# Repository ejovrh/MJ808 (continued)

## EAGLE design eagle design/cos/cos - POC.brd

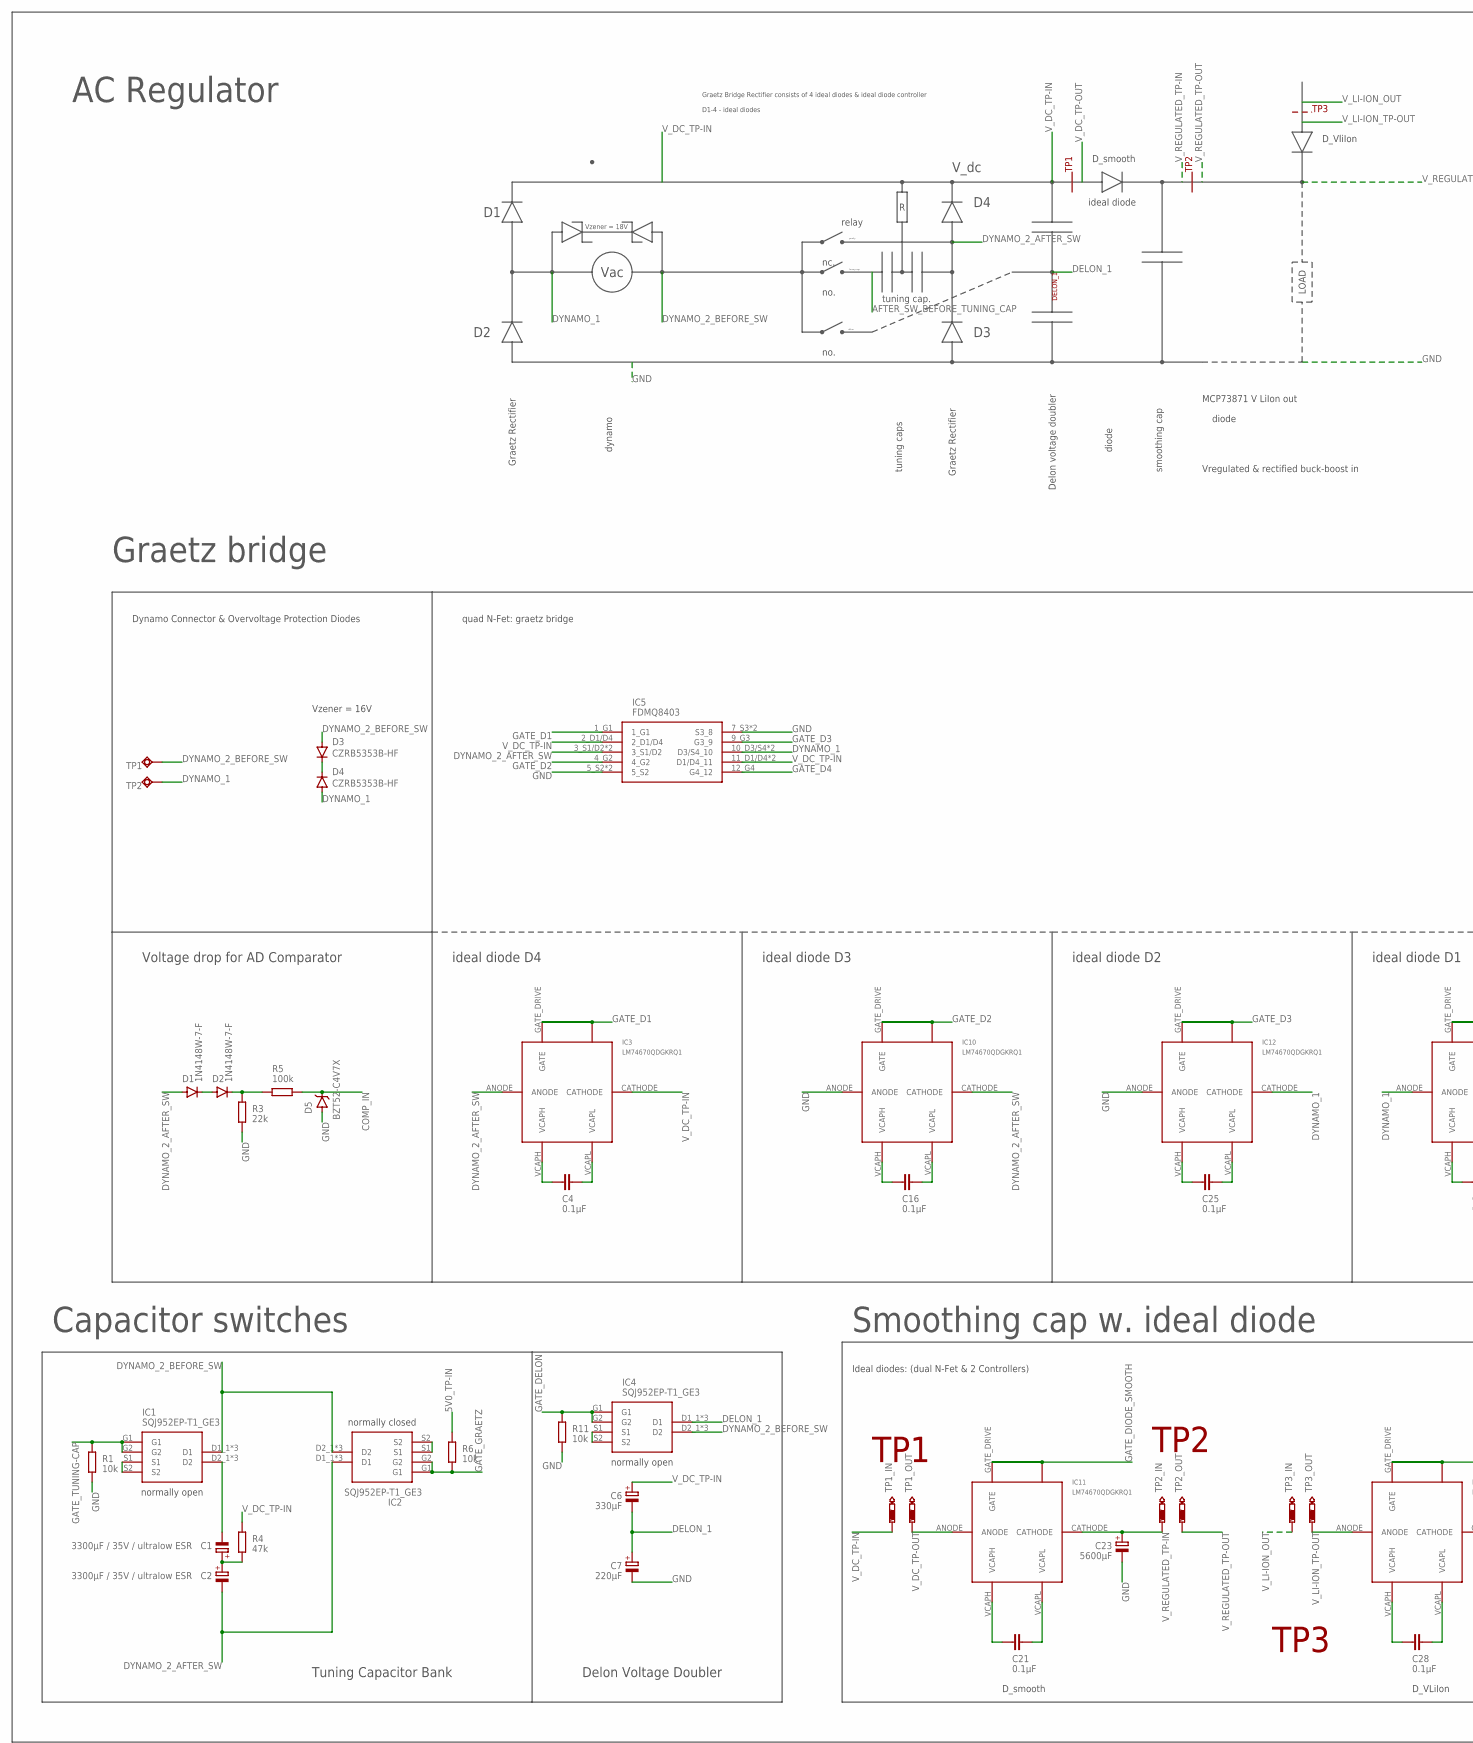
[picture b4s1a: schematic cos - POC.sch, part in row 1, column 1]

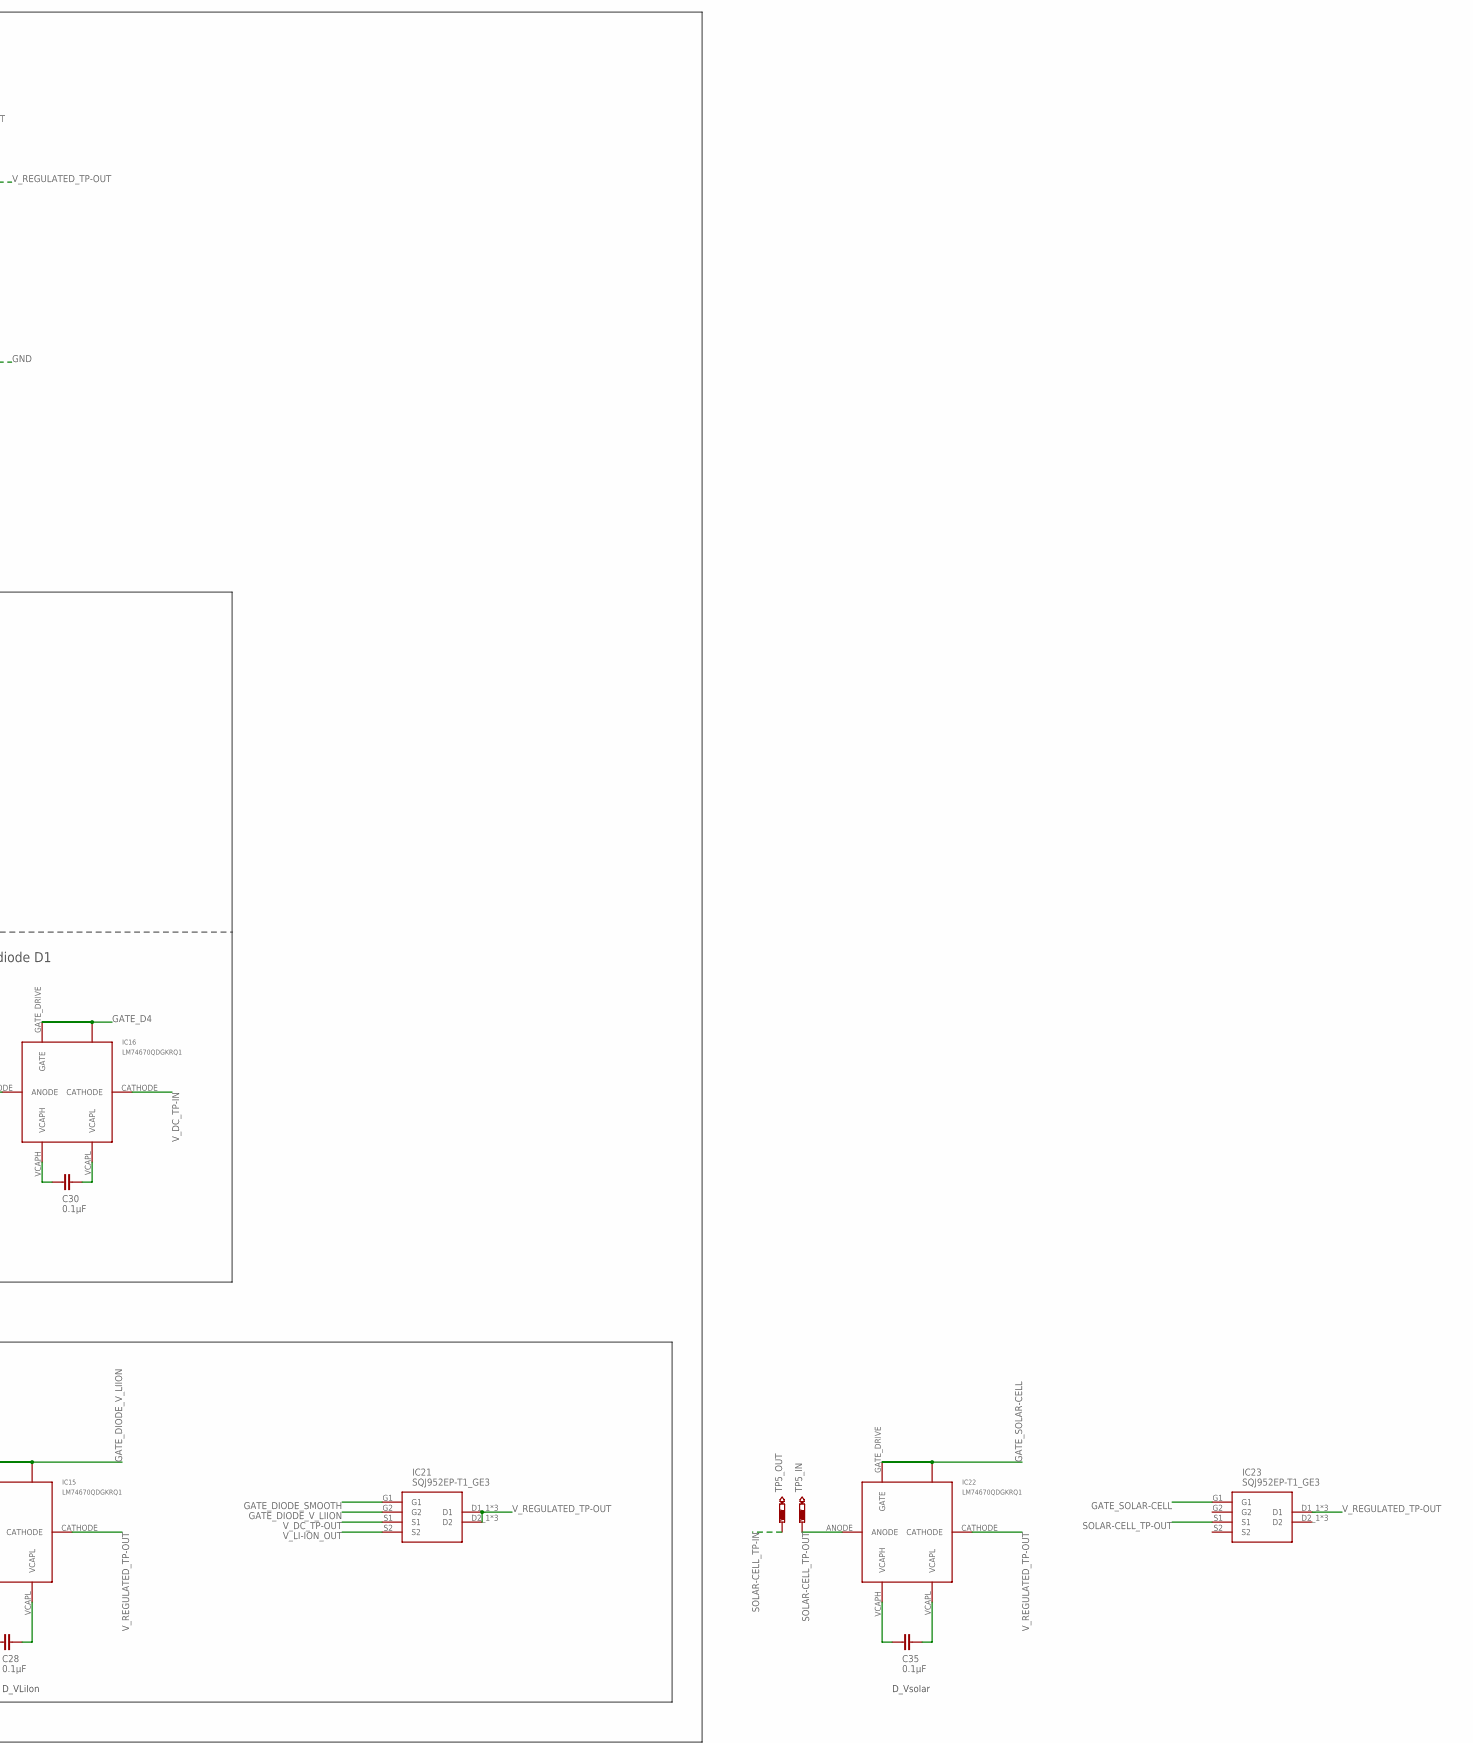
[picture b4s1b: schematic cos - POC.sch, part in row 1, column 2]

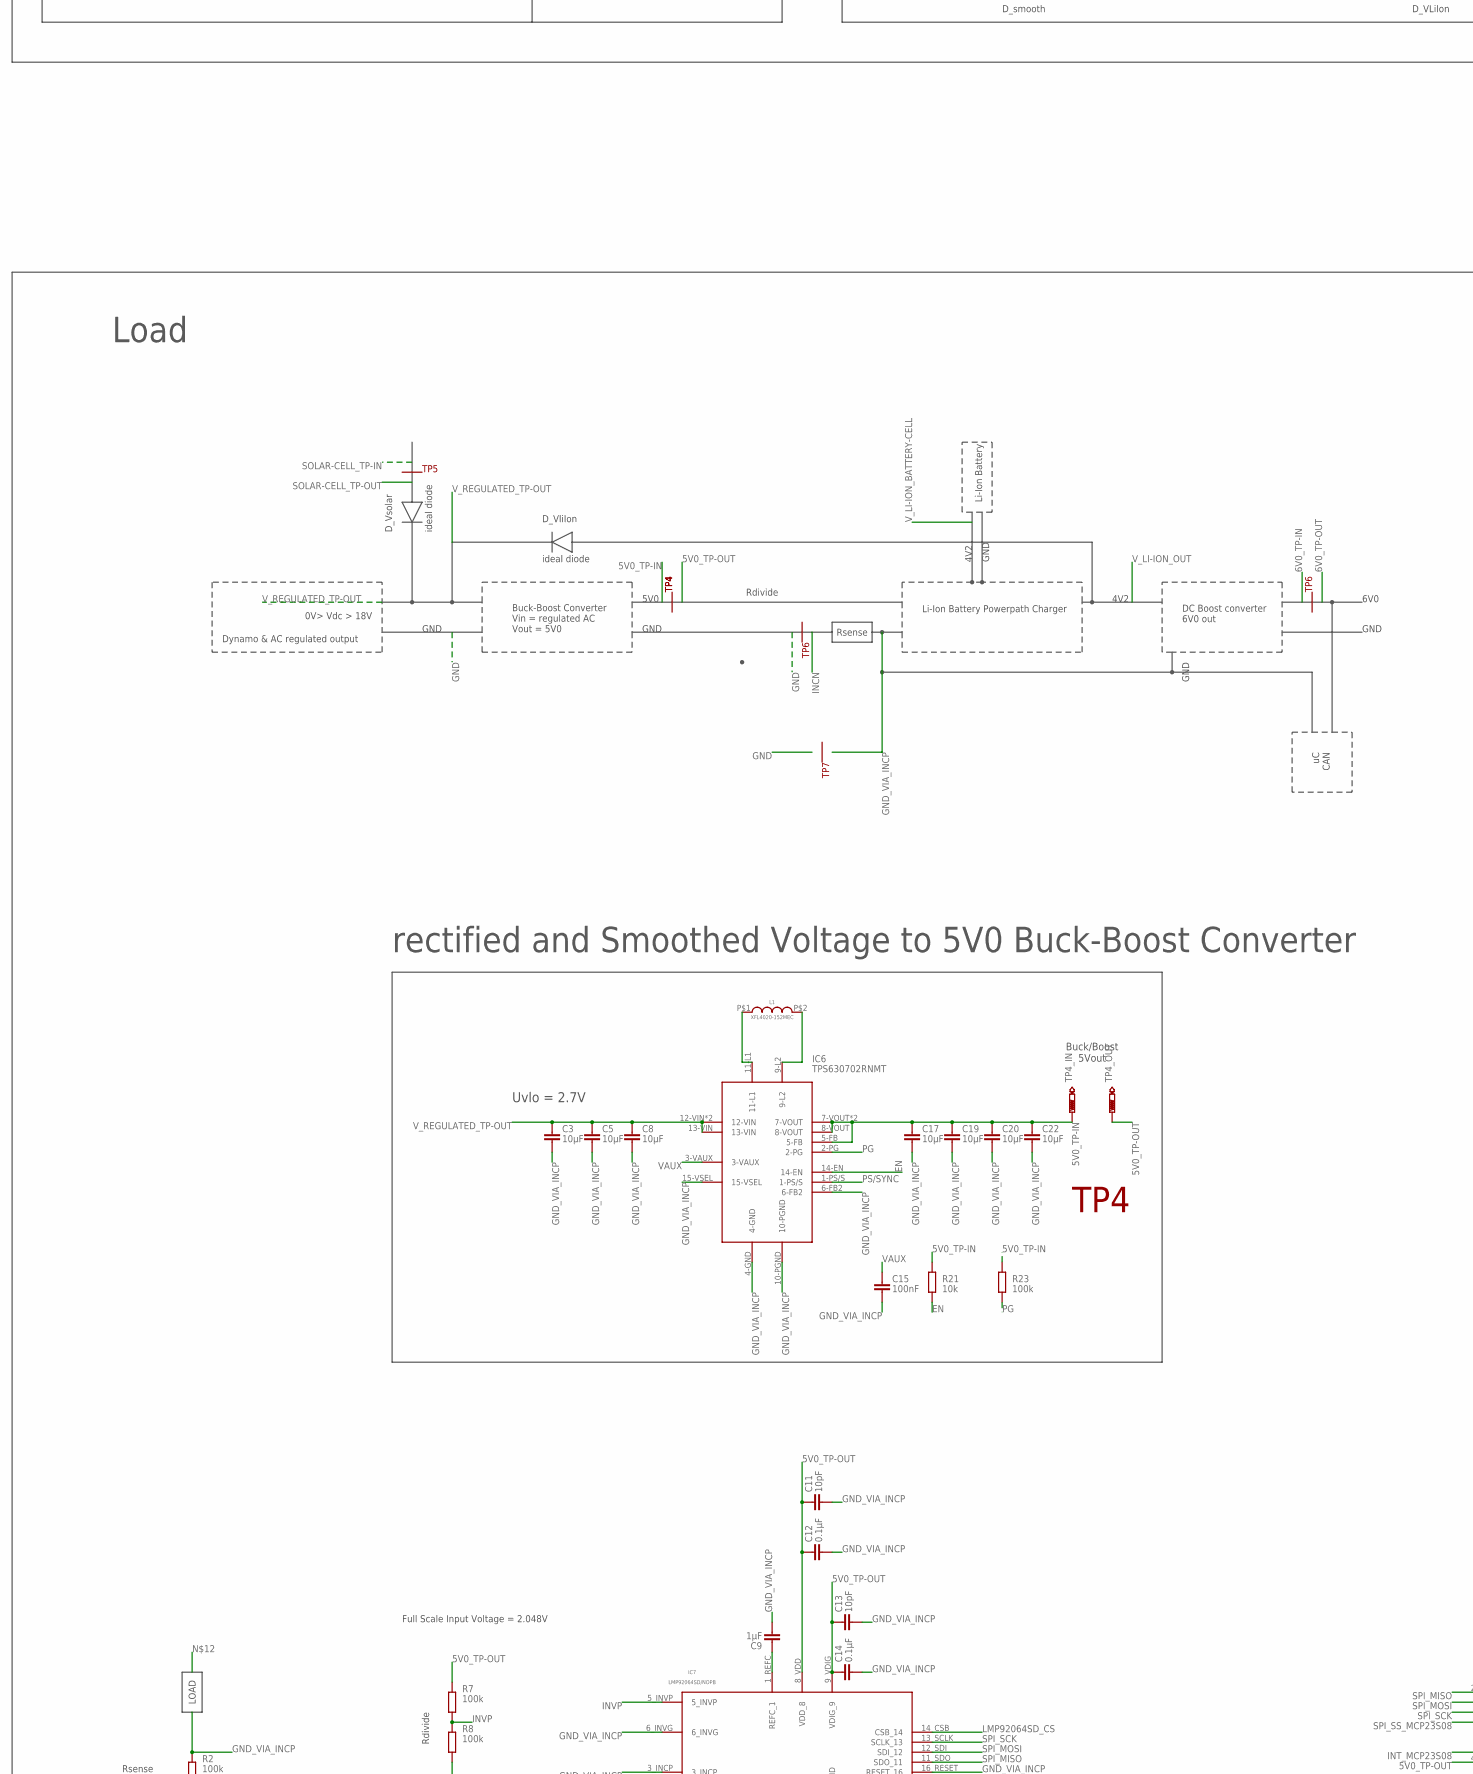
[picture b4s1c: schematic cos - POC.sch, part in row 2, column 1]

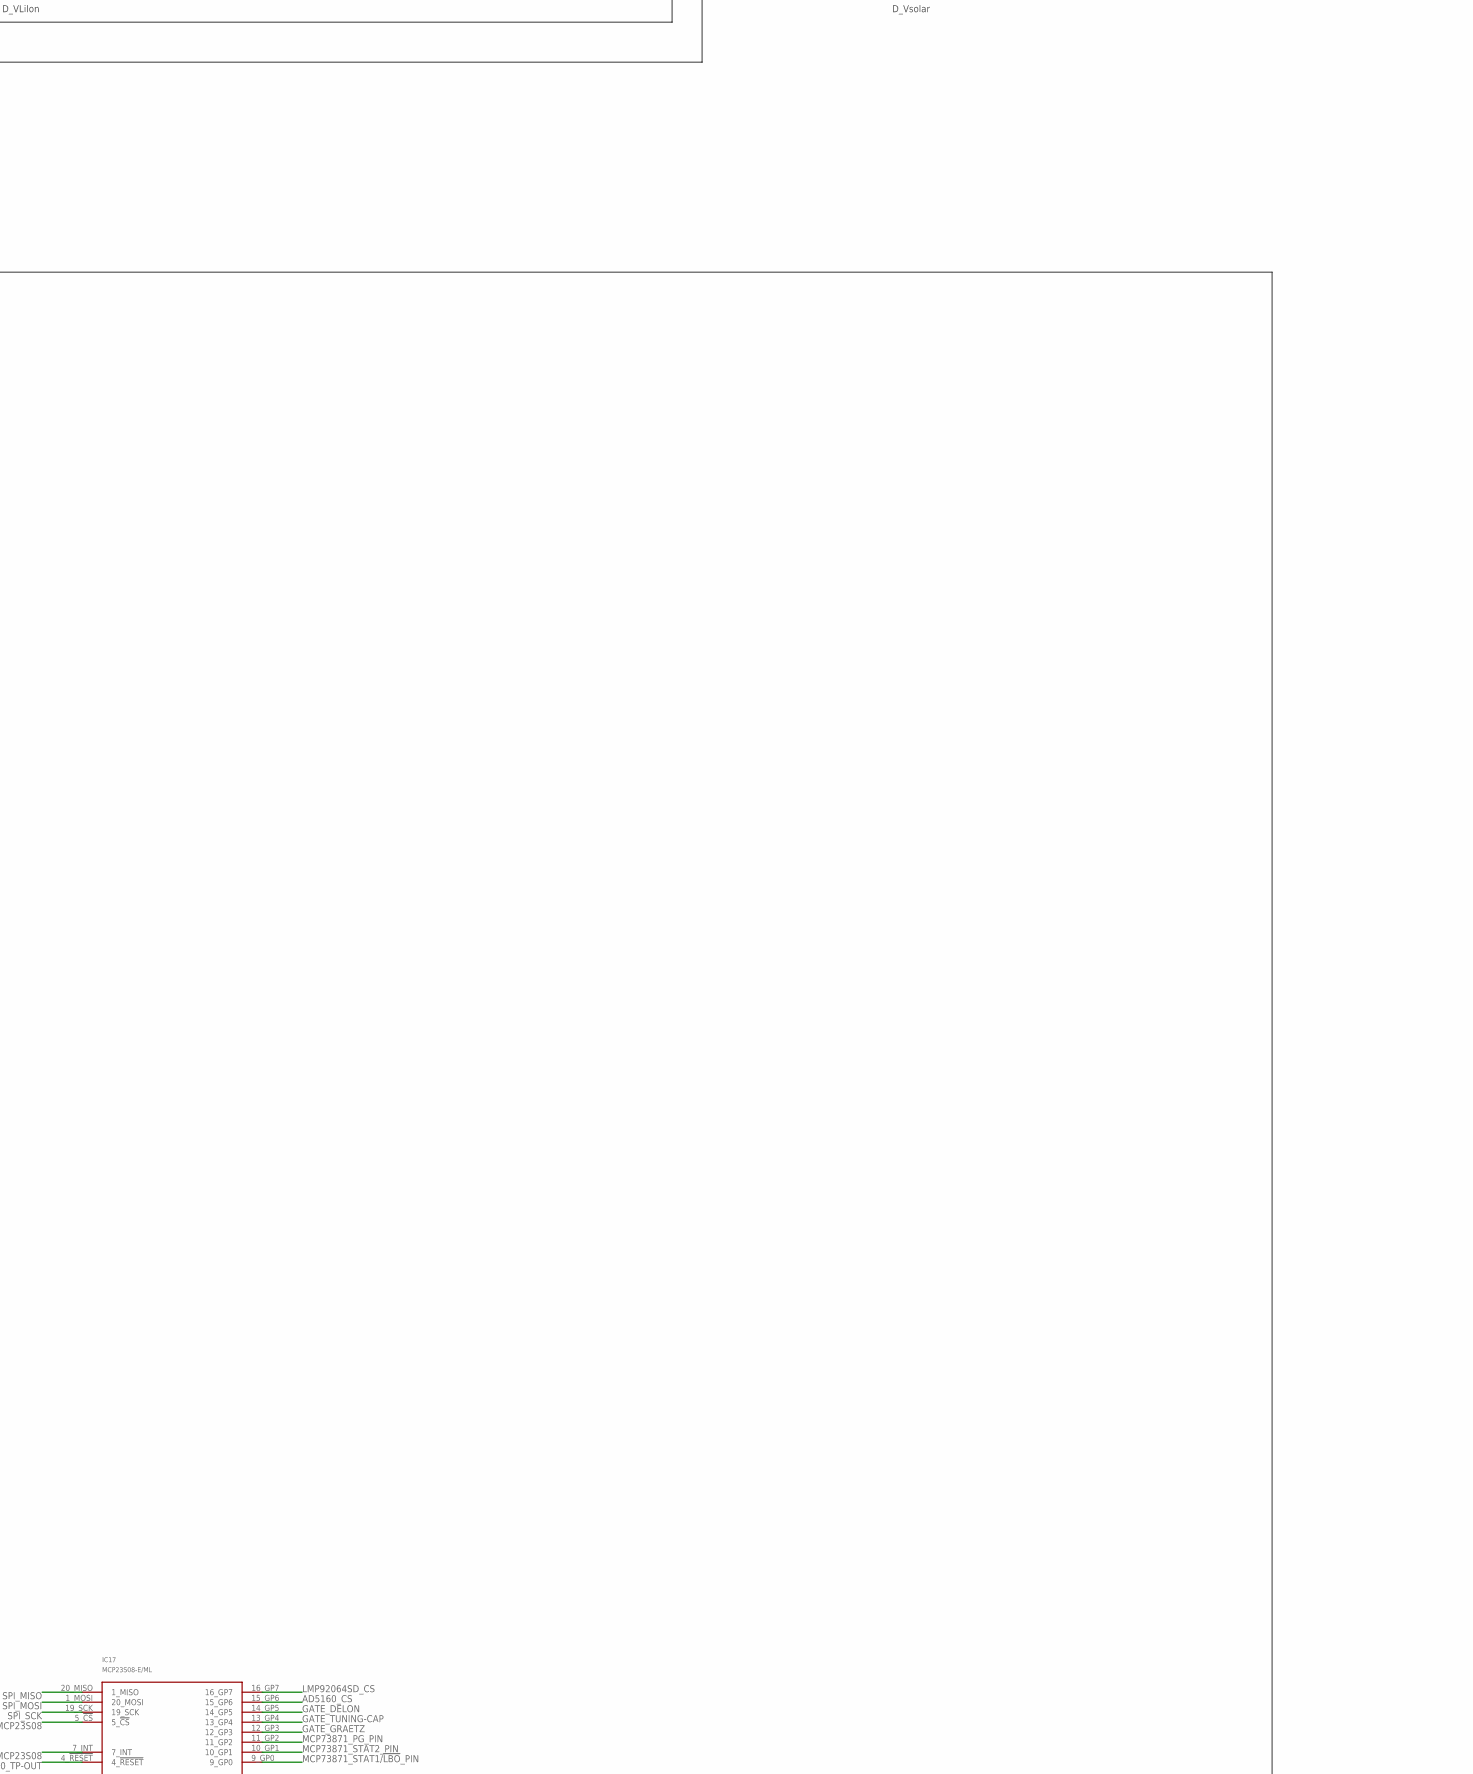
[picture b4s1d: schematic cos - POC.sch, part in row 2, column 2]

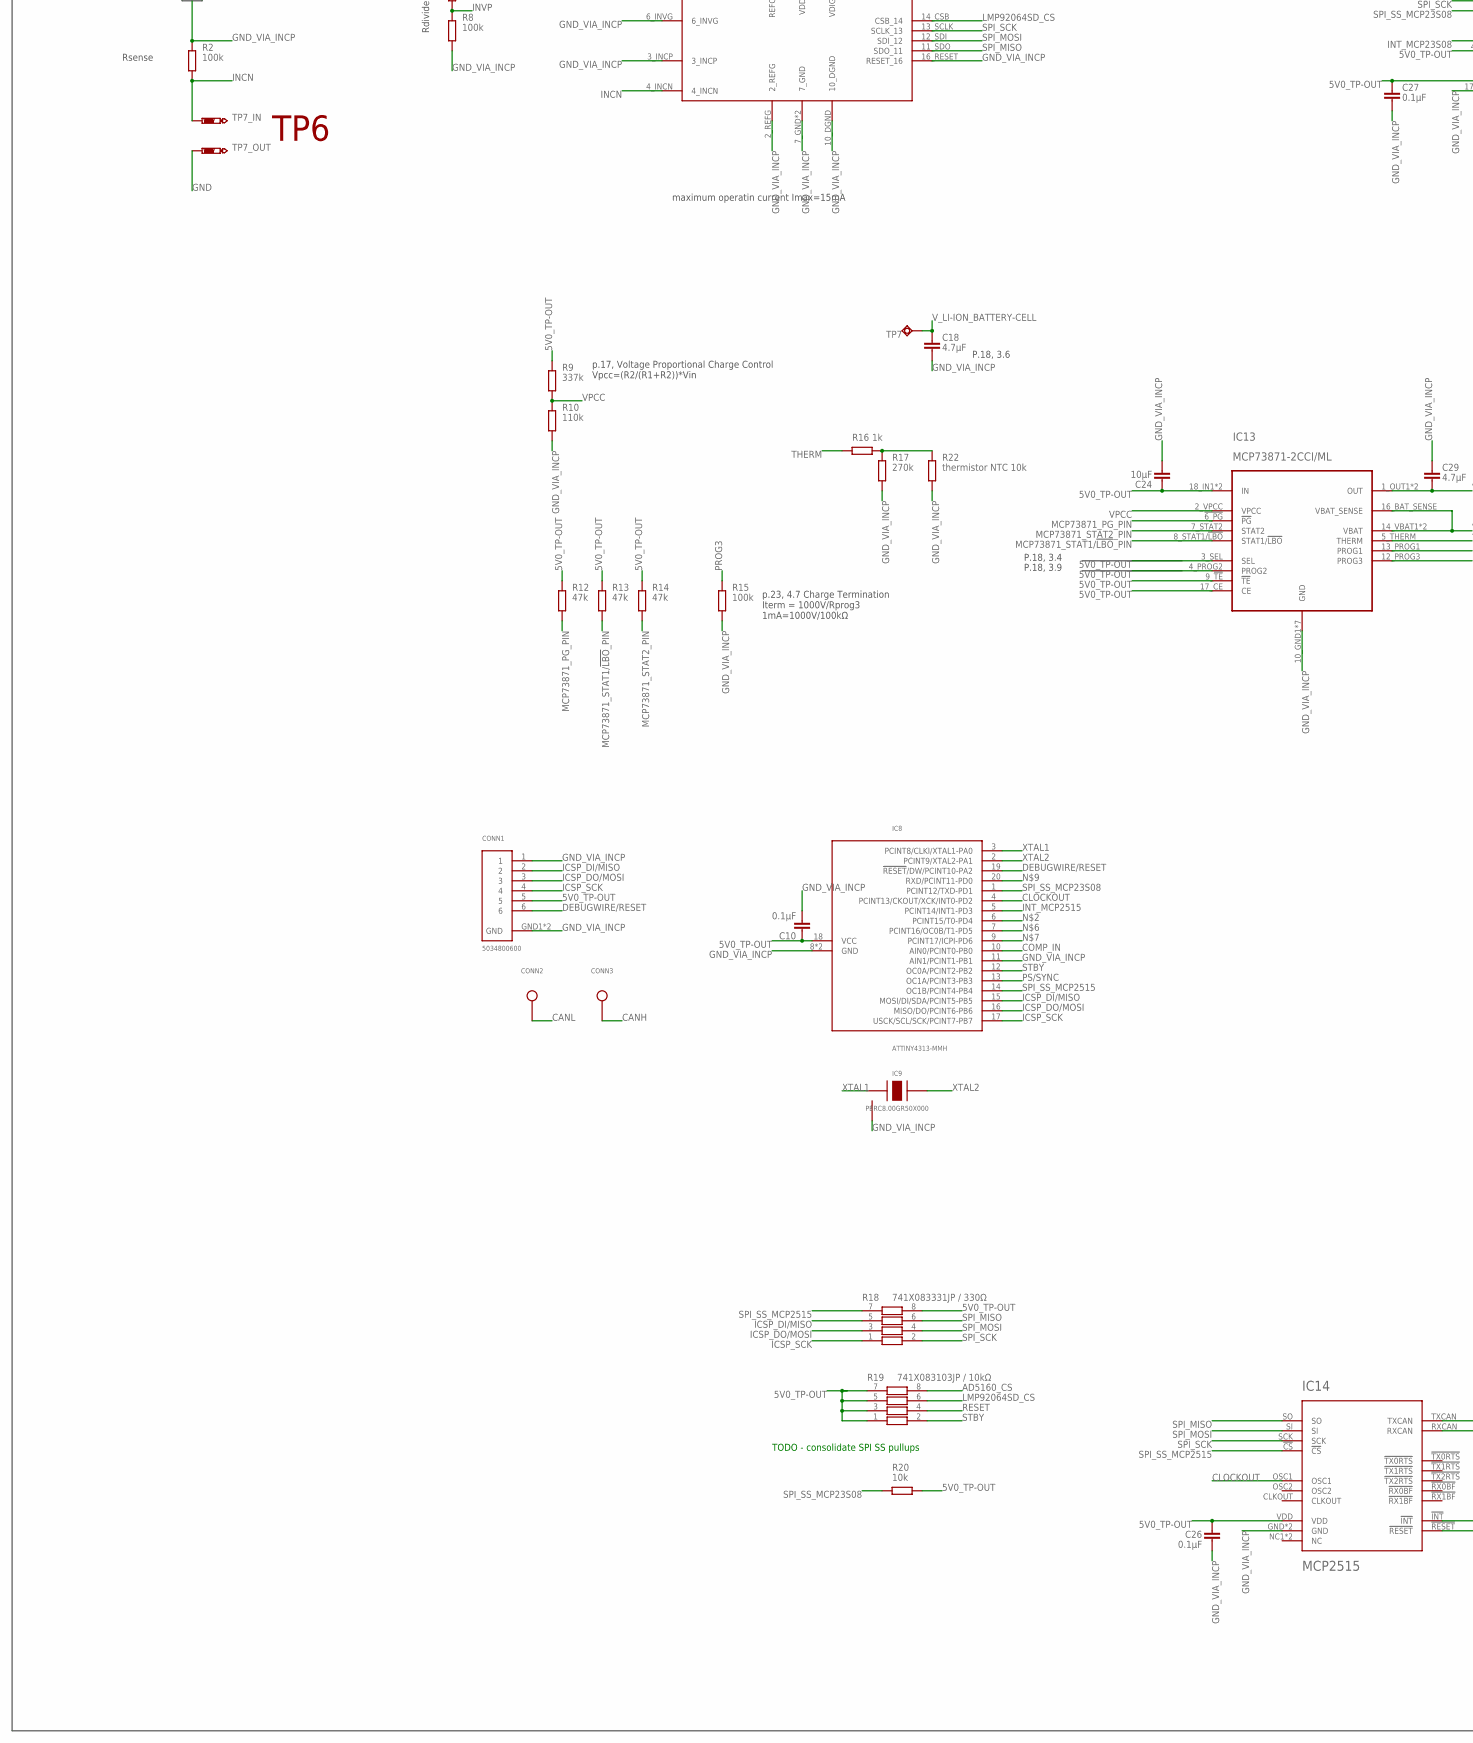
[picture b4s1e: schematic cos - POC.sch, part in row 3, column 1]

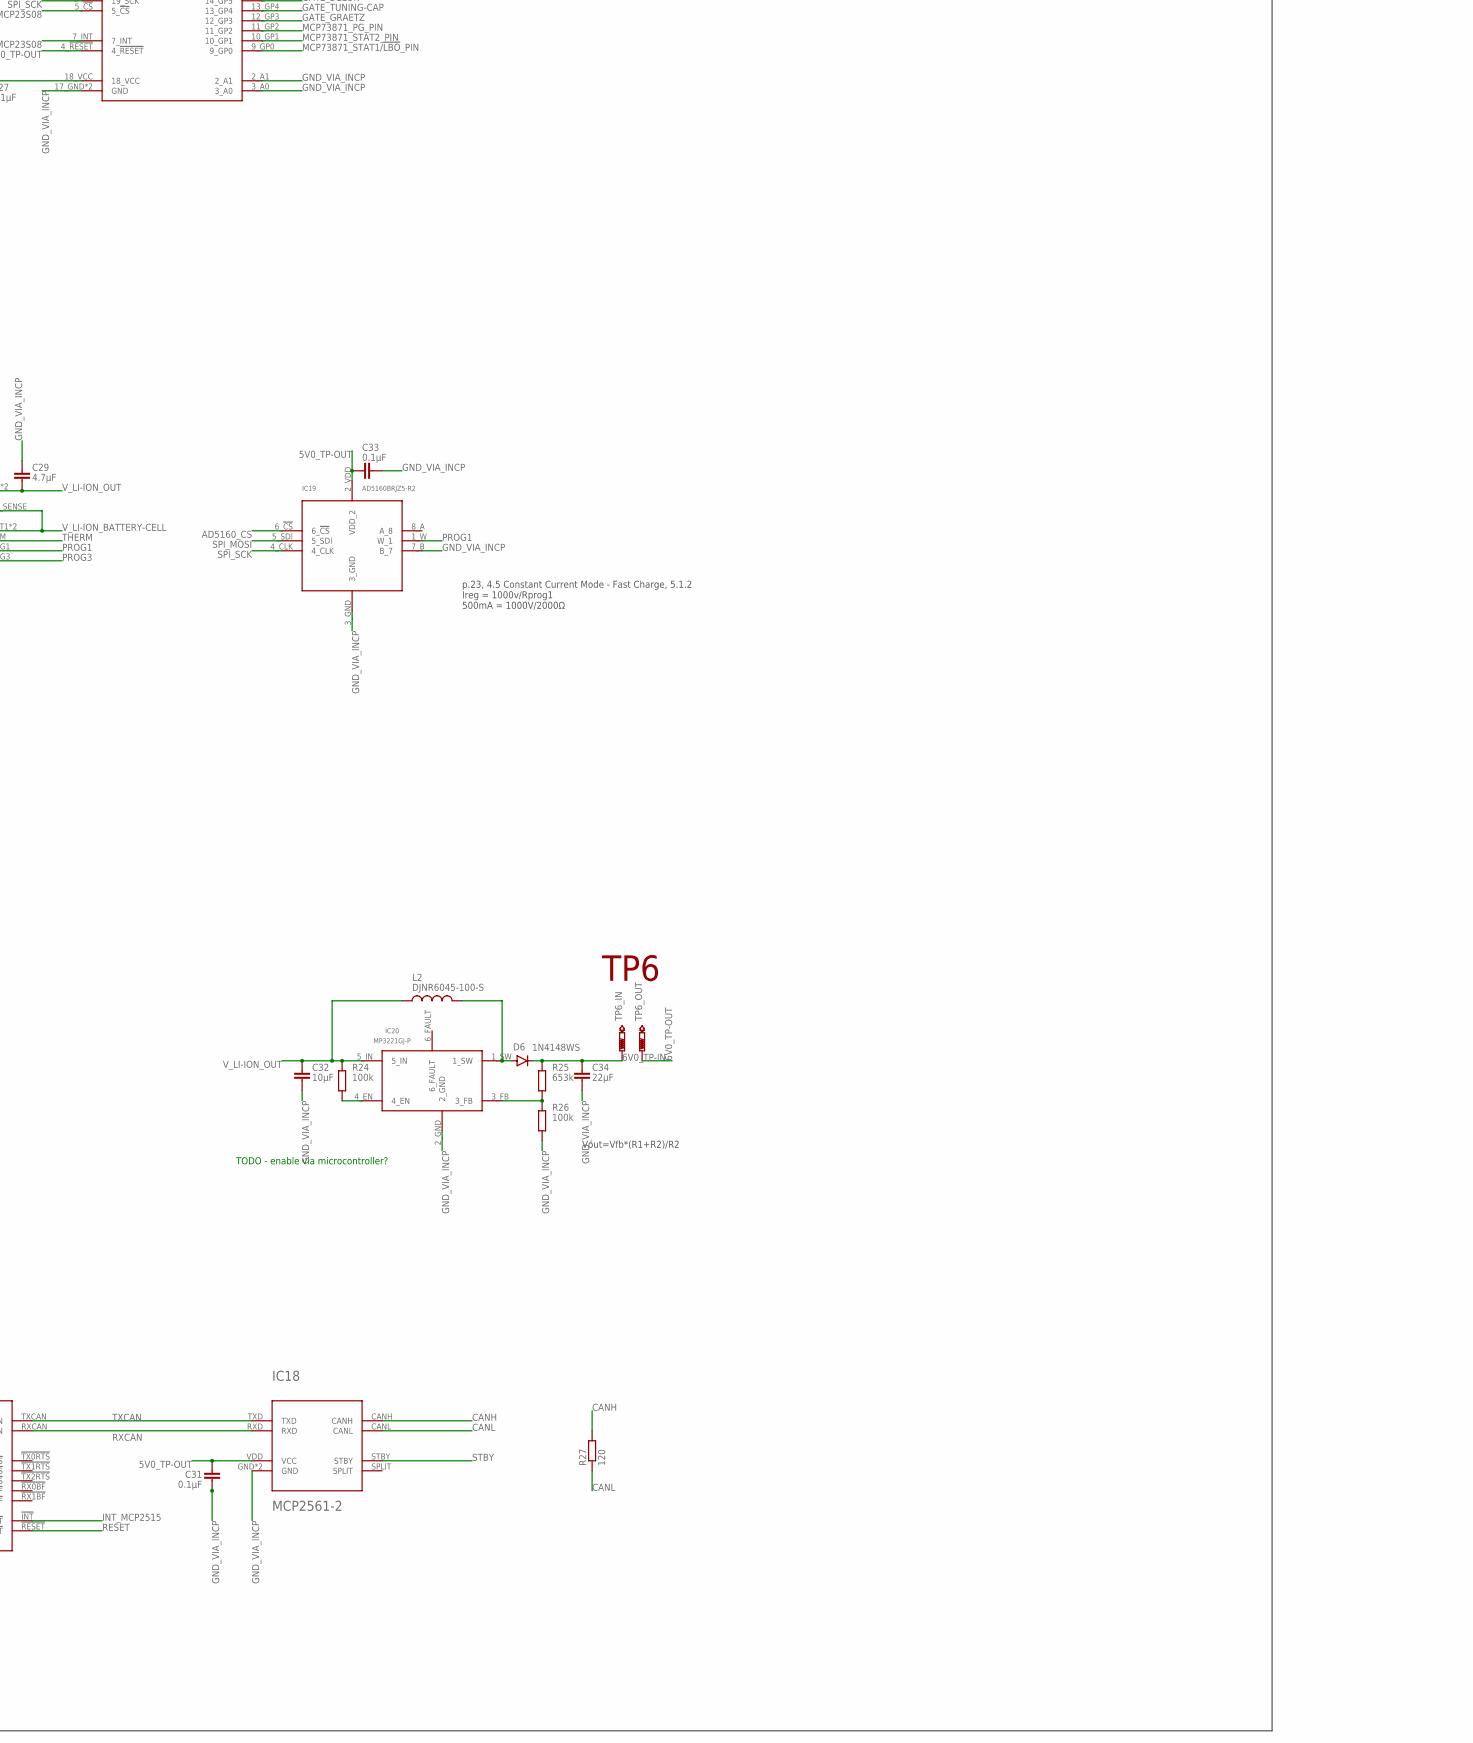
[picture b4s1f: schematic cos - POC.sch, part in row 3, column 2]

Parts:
C1, C2: 3300μF / 35V / ultralow ESR; E1,8-4
C3, C5, C19, C20, C22: 10μF; C0805
C4, C10, C12, C14, C16, C21, C25, C26, C27, C28, C30, C31, C33, C35: 0.1μF; C0402
C6: 330μF; E1,8-4
C7: 220μF; E1,8-4
C8, C17: 10μF; C0603
C9: 1μF; C0402
C11, C13: 10pF; C0402
C15: 100nF; C0402
C18, C29: 4.7μF; C0402
C23: 5600μF; E1,8-4
C24, C32: 10μF; C0402
C34: 22μF; C0402
CONN1: 5034800600; SMT
CONN2: CAN Low; SMT-1.2MM
CONN3: CAN High; SMT-1.2MM
D1, D2: 1N4148W-7-F; SOD-123_MINI-SMA
D3, D4: CZRB5353B-HF; DO214AA
D5: BZT52-C4V7X; SOD-123
D6: 1N4148WS; SOD-323
IC1, IC2, IC4, IC21, IC23: SQJ952EP-T1_GE3; SO-8L
IC3, IC10, IC11, IC12, IC15, IC16, IC22: LM74670QDGKRQ1; VSSOP-8
IC5: FDMQ8403; MLP-12
IC6: TPS630702RNMT; VQFN
IC7: LMP92064SD/NOPB; WSON-16
IC8: ATTINY4313-MMH; VQFN-20
IC9: PBRC8.00GR50X000; SMT
IC13: MCP73871-2CCI/ML; QFN50P400X400X100-21N
IC14: MCP2515; QFN20
IC17: MCP23S08-E/ML; QFN20
IC18: MCP2561-2; DFN10
IC19: AD5160BRJZ5-R2; SOT-23-8
IC20: MP3221GJ-P; TSOT23-6
L1: XFL4020-152MEC; SMD
L2: DJNR6045-100-S
R1, R6, R11, R20, R21: 10k; R0402
R2, R7, R8: 100k; R1206
R3: 22k; R0402
R4, R12, R13, R14: 47k; R0402
R5, R15, R23, R24, R26: 100k; R0402
R9: 337k; R0402
R10: 110k; R0402
R16: 1k; R0402
R17: 270k; R0402
R18: 741X083331JP / 330Ω; 0402
R19: 741X083103JP / 10kΩ; 0402
R22: thermistor NTC 10k; V526-0
R25: 653k; R0402
R27: 120; R0402
TP1, TP2, TP7: Li-Ion Cell +; P1-13
TP1_IN, TP1_OUT, TP2_IN, TP2_OUT, TP3_IN, TP3_OUT, TP4_IN, TP4_OUT, TP5_IN, TP5_OUT, TP6_IN, TP6_OUT, TP7_IN, TP7_OUT: PTR1TP10SQ; TP10SQ

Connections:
5V0_TP-IN: C17.1, C19.1, C20.1, C22.1, IC6.5-FB, IC6.7-VOUT, IC6.8-VOUT, IC6.VOUT (7-VOUT), R6.2, R21.2, R23.2, TP4_IN.TP
5V0_TP-OUT: C10.1, C11.1, C12.1, C13.1, C14.1, C24.1, C26.1, C27.1, C31.1, C33.1, CONN1.5, IC7.8_VDD (VDD_8), IC7.9_VDIG (VDIG_9), IC8.18 (VCC), IC13.3_SEL (SEL), IC13.4_PROG2 (PROG2), IC13.9_!TE! (!TE!), IC13.17_CE (CE), IC13.18_IN1 (IN), IC13.19_IN2 (IN), IC14.VDD, IC17.4_!RESET!, IC17.18_VCC, IC18.VDD (VCC), IC19.2_VDD (VDD_2), R7.2, R9.2, R12.2, R13.2, R14.2, R18.8, R19.1, R19.3, R19.5, R19.7, R20.2, TP4_OUT.TP
6V0_TP-IN: C34.1, D6.C, R25.2, TP6_IN.TP
6V0_TP-OUT: TP6_OUT.TP
AD5160_CS: IC17.15_GP6, IC19.6_!CS!, R19.8
AFTER_SW_BEFORE_TUNING_CAP: C1.-, IC1.D2_1 (D2), IC1.D2_2 (D2), IC1.D2_3 (D2)
CANH: CONN3.P$1, IC18.CANH, R27.2
CANL: CONN2.P$1, IC18.CANL, R27.1
CLOCKOUT: IC8.4 (PCINT13/CKOUT/XCK/INT0-PD2), IC14.OSC1
COMP_IN: D5.C, IC8.10 (AIN0/PCINT0-PB0), R5.2
D1_VCAPH: C4.2, IC3.VCAPH
D1_VCAPL: C4.1, IC3.VCAPL
D2_VCAPH: C16.2, IC10.VCAPH
D2_VCAPL: C16.1, IC10.VCAPL
D3_VCAPH: C25.2, IC12.VCAPH
D3_VCAPL: C25.1, IC12.VCAPL
D4_VCAPH: C30.2, IC16.VCAPH
D4_VCAPL: C30.1, IC16.VCAPL
DEBUGWIRE/RESET: CONN1.6, IC8.19 (!RESET!/DW/PCINT10-PA2)
DELON_1: C6.-, C7.+, IC4.D1_1 (D1), IC4.D1_2 (D1), IC4.D1_3 (D1)
DYNAMO_1: D4.A, IC5.10_D3/S4 (D3/S4_10), IC5.D3/S4 (D3/S4_10), IC12.CATHODE, IC16.ANODE, TP2.TP
DYNAMO_2_AFTER_SW: C2.-, D1.A, IC2.D1_1 (D1), IC2.D1_2 (D1), IC2.D1_3 (D1), IC3.ANODE, IC5.3_S1/D2, IC5.S1/D2 (3_S1/D2), IC10.CATHODE
DYNAMO_2_BEFORE_SW: D3.A, IC1.D1_1 (D1), IC1.D1_2 (D1), IC1.D1_3 (D1), IC2.D2_1 (D2), IC2.D2_2 (D2), IC2.D2_3 (D2), IC4.D2_1 (D2), IC4.D2_2 (D2), IC4.D2_3 (D2), TP1.TP
D_SMOOTH_VCAP: C21.1, IC11.VCAPL
D_SMOOTH_VCAPH: C21.2, IC11.VCAPH
D_VLIION_VCAPH: C28.2, IC15.VCAPH
D_VLIION_VCAPH1: C35.2, IC22.VCAPH
D_VLIION_VCAPL: C28.1, IC15.VCAPL
D_VLIION_VCAPL1: C35.1, IC22.VCAPL
EN: IC6.14-EN, R21.1
EN2: IC20.4_EN, R24.1
FB: IC20.3_FB, R25.1, R26.2
GATE_D1: IC3.GATE_DRIVE (GATE), IC3.GATE_PULLD, IC5.1_G1
GATE_D2: IC5.4_G2, IC10.GATE_DRIVE (GATE), IC10.GATE_PULLD
GATE_D3: IC5.9_G3 (G3_9), IC12.GATE_DRIVE (GATE), IC12.GATE_PULLD
GATE_D4: IC5.12_G4 (G4_12), IC16.GATE_DRIVE (GATE), IC16.GATE_PULLD
GATE_DELON: IC4.G1, IC4.G2, IC17.14_GP5, R11.2
GATE_DIODE_SMOOTH: IC11.GATE_DRIVE (GATE), IC11.GATE_PULLD, IC21.G1
GATE_DIODE_V_LIION: IC15.GATE_DRIVE (GATE), IC15.GATE_PULLD, IC21.G2
GATE_GRAETZ: IC2.G1, IC2.G2, IC17.12_GP3, R6.1
GATE_SOLAR-CELL: IC22.GATE_DRIVE (GATE), IC22.GATE_PULLD, IC23.G1
GATE_TUNING-CAP: IC1.G1, IC1.G2, IC17.13_GP4, R1.2
GND: C7.-, C23.-, D5.A, IC5.5_S2, IC5.6_S2 (5_S2), IC5.7_S3 (S3_8), IC5.8_S3 (S3_8), IC10.ANODE, IC12.ANODE, R1.1, R3.1, R11.1, TP7_OUT.TP
GND_VIA_INCP: C3.2, C5.2, C8.2, C9.2, C10.2, C11.2, C12.2, C13.2, C14.2, C15.2, C17.2, C18.2, C19.2, C20.2, C22.2, C24.2, C26.2, C27.2, C29.1, C31.2, C32.2, C33.2, C34.2, CONN1.1, CONN1.GND1 (GND), CONN1.GND2 (GND), IC6.4-GND, IC6.6-FB2, IC6.10-PGND, IC6.15-VSEL, IC7.2_REFG, IC7.3_INCP, IC7.6_INVG, IC7.7_GND, IC7.10_DGND, IC7.16_RESET (RESET_16), IC7.GND1 (7_GND), IC8.8 (GND), IC8.11 (AIN1/PCINT1-PB1), IC8.GND, IC9.GND, IC13.10_GND1 (GND), IC13.11_GND2 (GND), IC13.GND2 (GND), IC13.GND3 (GND), IC13.GND4 (GND), IC13.GND5 (GND), IC13.GND6 (GND), IC14.GND, IC14.GND6 (GND), IC17.2_A1, IC17.3_A0, IC17.17_GND (GND), IC17.GND, IC18.GND, IC18.VSS (GND), IC19.3_GND, IC19.7_B (B_7), IC20.2_GND, R2.2, R8.1, R10.1, R15.1, R17.1, R22.1, R26.1
ICSP_DI/MISO: CONN1.2, IC8.15 (MOSI/DI/SDA/PCINT5-PB5), R18.5
ICSP_DO/MOSI: CONN1.3, IC8.16 (MISO/DO/PCINT6-PB6), R18.3
ICSP_SCK: CONN1.4, IC8.17 (USCK/SCL/SCK/PCINT7-PB7), R18.1
INCN: IC7.4_INCN, R2.1, TP7_IN.TP
INT_MCP23S08: IC17.7_INT
INT_MCP2515: IC8.5 (PCINT14/INT1-PD3), IC14.!INT!
INVP: IC7.5_INVP, R7.1, R8.2
LMP92064SD_CS: IC7.14_CSB (CSB_14), IC17.16_GP7, R19.6
MCP73871_PG_PIN: IC13.!6_PG! (!PG!), IC17.11_GP2, R12.1
MCP73871_STAT1/!LBO!_PIN: IC13.8_STAT1/!LBO! (STAT1/!LBO!), IC17.9_GP0, R13.1
MCP73871_STAT2_PIN: IC13.7_STAT2 (STAT2), IC17.10_GP1, R14.1
unnamed: IC6.11-L1, L1.P$1
unnamed: D1.C, D2.A
unnamed: D2.C, R3.2, R5.1
unnamed: IC6.9-L2, L1.P$2
unnamed: R16.2, R17.2, R22.2
unnamed: IC1.S1, IC1.S2
unnamed: IC2.S1, IC2.S2
unnamed: C9.1, IC7.1_REFC (REFC_1)
unnamed: IC4.S1, IC4.S2
PG: IC6.2-PG, R23.1
PROG1: IC13.13_PROG1 (PROG1), IC19.1_W (W_1)
PROG3: IC13.12_PROG3 (PROG3), R15.2
PS/SYNC: IC6.1-PS/S, IC8.13 (OC1A/PCINT3-PB3)
RESET: IC14.!RESET!, R19.4
RXCAN: IC14.RXCAN, IC18.RXD
SOLAR-CELL_TP-IN: TP5_OUT.TP
SOLAR-CELL_TP-OUT: IC22.ANODE, IC23.S1, TP5_IN.TP
SPI_MISO: IC7.11_SDO (SDO_11), IC14.SO, IC17.20_MISO (1_MISO), R18.6
SPI_MOSI: IC7.12_SDI (SDI_12), IC14.SI, IC17.1_MOSI (20_MOSI), IC19.5_SDI, R18.4
SPI_SCK: IC7.13_SCLK (SCLK_13), IC14.SCK, IC17.19_SCK, IC19.4_CLK, R18.2
SPI_SS_MCP23S08: IC8.1 (PCINT12/TXD-PD1), IC17.5_!CS!, R20.1
SPI_SS_MCP2515: IC8.14 (OC1B/PCINT4-PB4), IC14.!CS!, R18.7
STBY: IC8.12 (OC0A/PCINT2-PB2), IC18.STBY, R19.2
SW: D6.A, IC20.1_SW, L2.2
THERM: IC13.5_THERM (THERM), R16.1
TUNIN_CAP2_BIAS: C1.+, C2.+, R4.1
TXCAN: IC14.TXCAN, IC18.TXD
VAUX: C15.1, IC6.3-VAUX
VPCC: IC13.2_VPCC (VPCC), R9.1, R10.2
V_DC_TP-IN: C6.+, IC3.CATHODE, IC5.2_D1/D4, IC5.11_D1/D4 (D1/D4_11), IC5.D1/D4 (D1/D4_11), IC16.CATHODE, R4.2, TP1_IN.TP
V_DC_TP-OUT: IC11.ANODE, IC21.S1, TP1_OUT.TP
V_LI-ION_BATTERY-CELL: C18.1, IC13.14_VBAT1 (VBAT), IC13.15_VBAT2 (VBAT), IC13.16_BAT_SENSE (VBAT_SENSE), TP7.TP
V_LI-ION_OUT: C29.2, C32.1, IC13.1_OUT1 (OUT), IC13.20_OUT2 (OUT), IC20.5_IN, IC21.S2, L2.1, R24.2, TP3_IN.TP
V_LI-ION_TP-OUT: IC15.ANODE, TP3_OUT.TP
V_REGULATED_TP-IN: C23.+, IC11.CATHODE, TP2_IN.TP
V_REGULATED_TP-OUT: C3.1, C5.1, C8.1, IC6.12-VIN, IC6.13-VIN, IC6.VIN (12-VIN), IC15.CATHODE, IC21.D1_1 (D1), IC21.D1_2 (D1), IC21.D1_3 (D1), IC21.D2_1 (D2), IC21.D2_2 (D2), IC21.D2_3 (D2), IC22.CATHODE, IC23.D1_1 (D1), IC23.D1_2 (D1), IC23.D1_3 (D1), TP2_OUT.TP
XTAL1: IC8.3 (PCINT8/CLKI/XTAL1-PA0), IC9.XTAL1
XTAL2: IC8.2 (PCINT9/XTAL2-PA1), IC9.XTAL2
ZENER_COMMON: D3.C, D4.C

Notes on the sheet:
P.18, 3.6
p.23, 4.5 Constant Current Mode - Fast Charge, 5.1.2 Ireg = 1000v/Rprog1 500mA = 1000V/2000Ω
p.23, 4.7 Charge Termination Iterm = 1000V/Rprog3 1mA=1000V/100kΩ
p.17, Voltage Proportional Charge Control Vpcc=(R2/(R1+R2))*Vin
P.18, 3.4
P.18, 3.9
Vout=Vfb*(R1+R2)/R2
Vzener = 16V
ideal diode D1
ideal diode D2
ideal diode D3
ideal diode D4
Tuning Capacitor Bank
Delon Voltage Doubler
quad N-Fet: graetz bridge
V_dc
Vac
Graetz Bridge Rectifier consists of 4 ideal diodes & ideal diode controller D1-4 - ideal diodes
tuning cap.
Dynamo Connector & Overvoltage Protection Diodes
smoothing cap
LOAD
Graetz Rectifier
Delon voltage doubler
relay
nc.
no.
normally open
normally closed
TODO - enable via microcontroller?
ideal diode
TP1
TP2
AC Regulator
Load
rectified and Smoothed Voltage to 5V0 Buck-Boost Converter
Buck-Boost Converter Vin = regulated AC Vout = 5V0
5V0
GND
Dynamo & AC regulated output

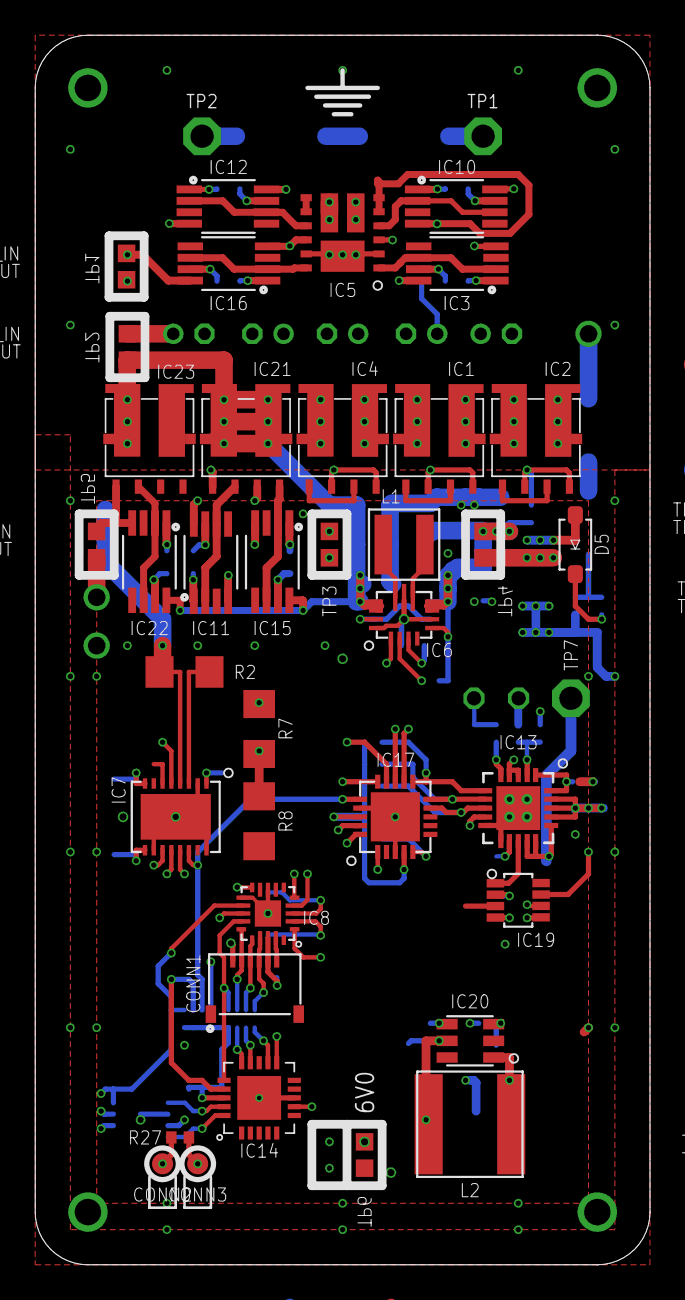
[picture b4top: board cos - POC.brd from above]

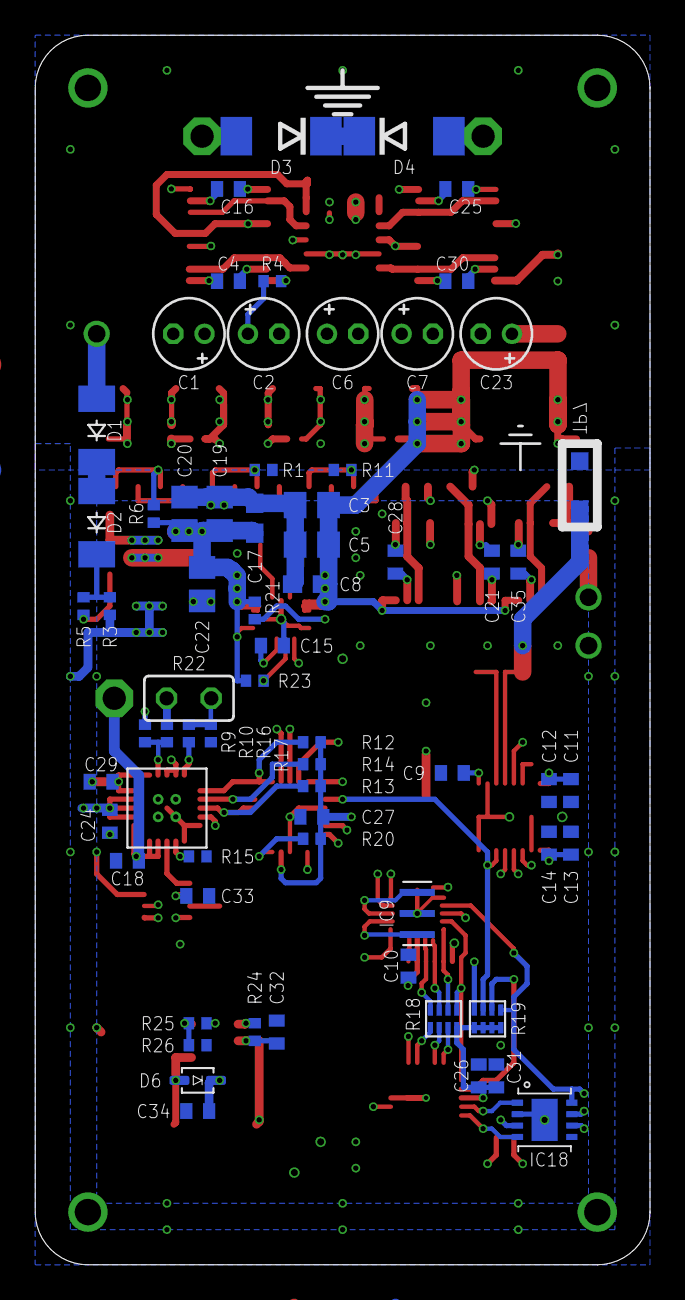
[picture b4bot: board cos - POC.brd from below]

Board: 4 copper layers, 35.0 x 70.0 mm, 113 parts (67 on the bottom side), 91 nets.
